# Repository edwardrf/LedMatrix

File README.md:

# LedMatrix
=======
8x8 Led Matrix project with microphone, light sensor and accelerometer

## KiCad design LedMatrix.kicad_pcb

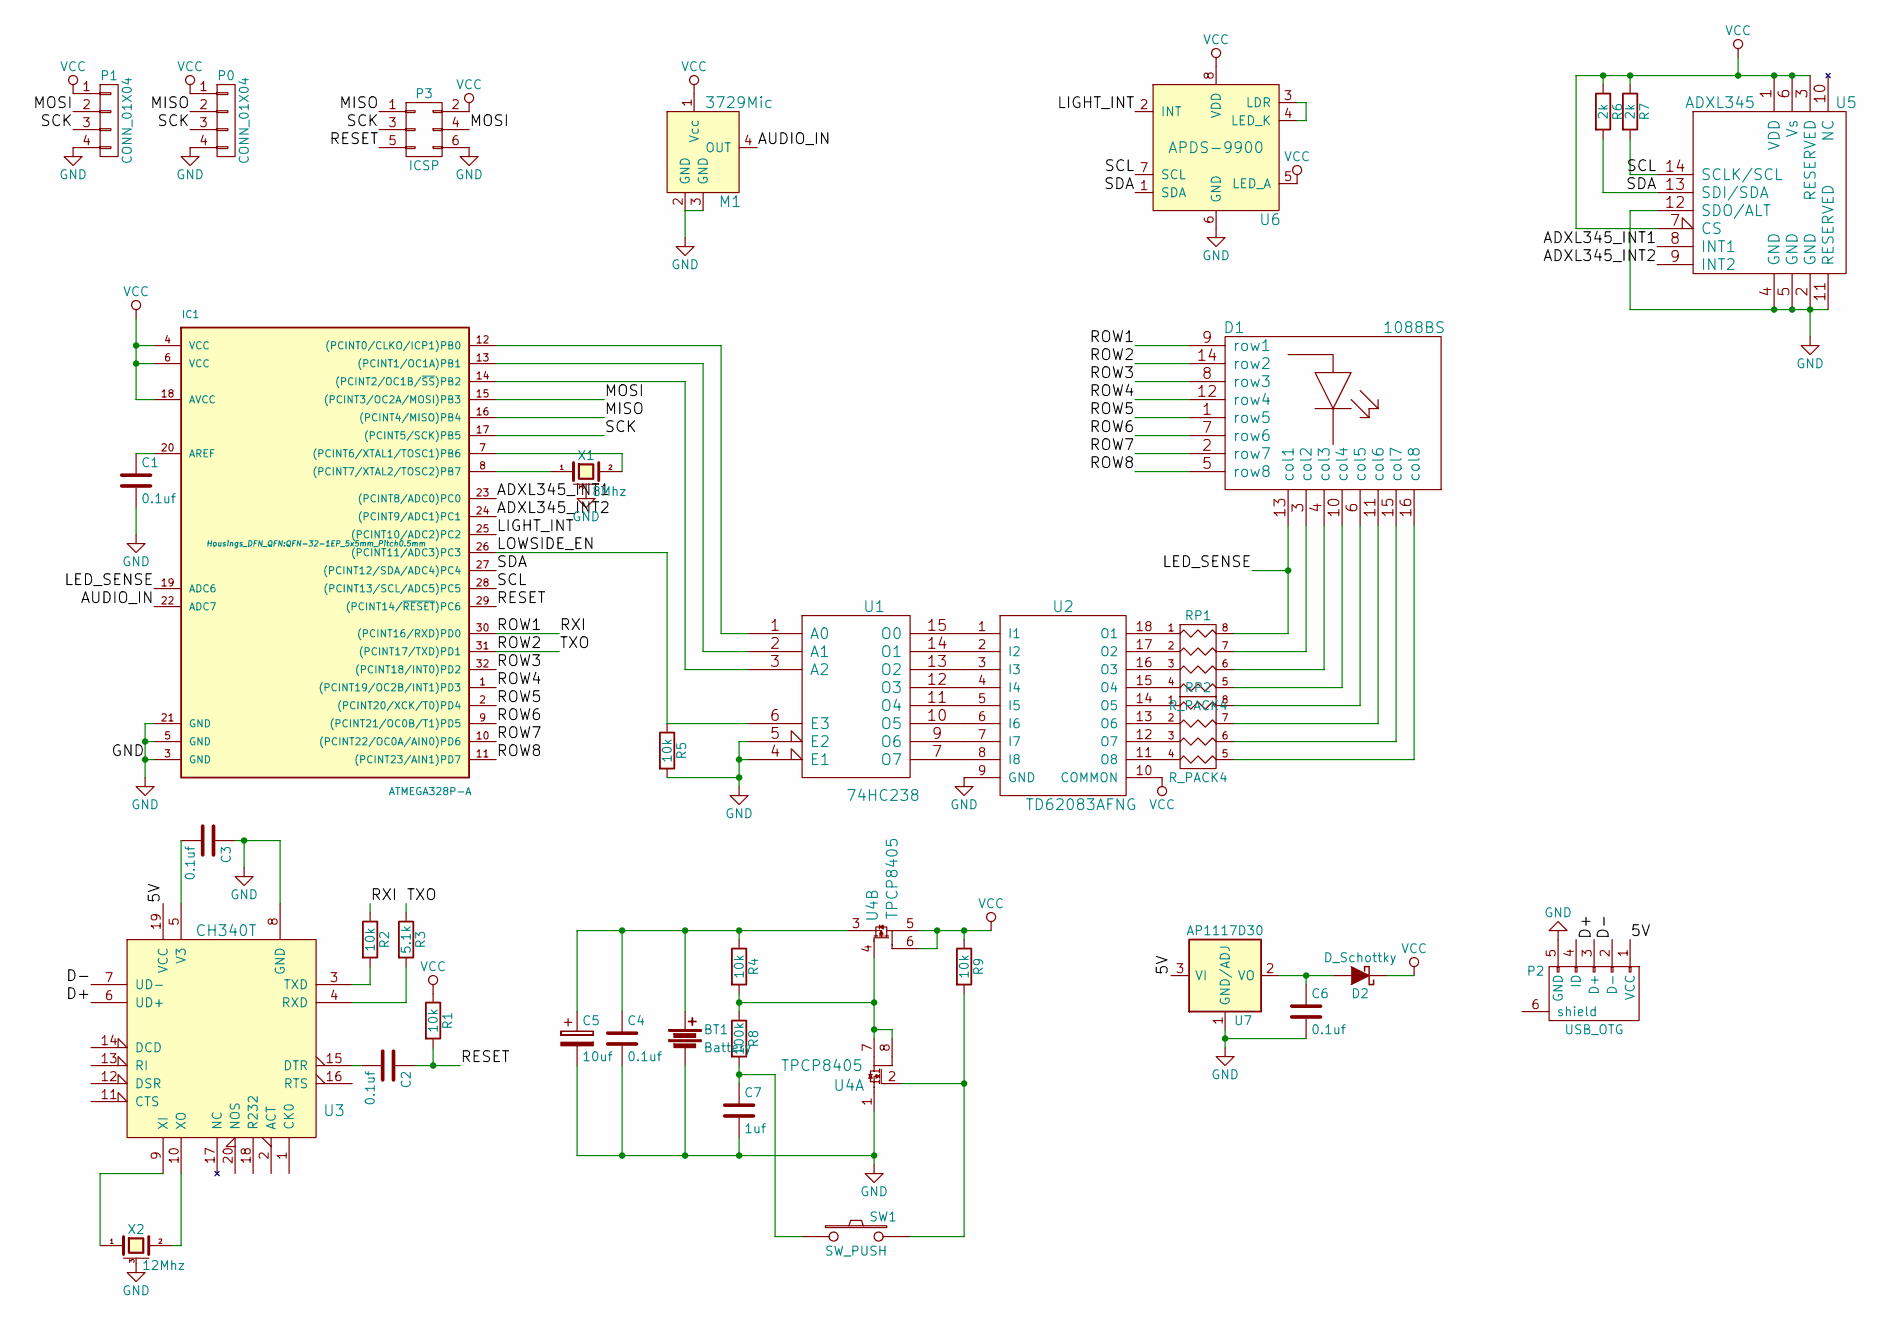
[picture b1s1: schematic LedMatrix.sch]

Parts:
BT1: Battery; CR2032-S8421-45R
C1, C2, C3, C4, C6: 0.1uf; C_0603
C5: 10uf; TantalC_SizeR_EIA-2012
C7: 1uf; C_0603
D1: 1088BS; 8X8 LED 32mm
D2: D_Schottky; SMA_Standard
IC1: ATMEGA328P-A; QFN-32-1EP_5x5mm_Pitch0.5mm
M1: 3729Mic
P0, P1: CONN_01X04; Pin_Header_Straight_1x04
P2: USB_OTG; 47589-0001
P3: ICSP; Pin_Header_Straight_2x03
R1, R2, R4, R5, R9: 10k; R_0603
R3: 5.1k; R_0603
R6, R7: 2k; R_0603
R8: 100k; R_0603
RP1, RP2: R_PACK4; R_Array_Concave_4x0603
SW1: SW_PUSH; SKSCLCE010
U1: 74HC238; TSSOP-16_4.4x5mm_Pitch0.65mm
U2: TD62083AFNG; TSSOP-14_4.4x5mm_Pitch0.65mm
U3: CH340T; SSOP-20_5.3x7.2mm_Pitch0.65mm
U4: TPCP8405; PS-8
U5: ADXL345
U6: APDS-9900; ADPS-9900
U7: AP1117D30; SOT-223
X1: 8Mhz; CSTCE8M00G52
X2: 12Mhz; CSTCE8M00G52

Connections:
/5V: P2.1 (VCC), U3.19 (VCC), U7.3 (VI)
/ADXL345_INT1: IC1.23 ((PCINT8/ADC0)PC0), U5.8 (INT1)
/ADXL345_INT2: IC1.24 ((PCINT9/ADC1)PC1), U5.9 (INT2)
/AUDIO_IN: IC1.22 (ADC7), M1.4 (OUT)
/D+: P2.3 (D+), U3.6 (UD+)
/D-: P2.2 (D-), U3.7 (UD-)
/LED_SENSE: D1.13 (col1), IC1.19 (ADC6), RP1.8 (R1)
/LIGHT_INT: IC1.25 ((PCINT10/ADC2)PC2), U6.2 (INT)
/LOWSIDE_EN: IC1.26 ((PCINT11/ADC3)PC3), R5.1, U1.6 (E3)
/MISO: IC1.16 ((PCINT4/MISO)PB4), P0.2, P3.1
/MOSI: IC1.15 ((PCINT3/OC2A/MOSI)PB3), P1.2, P3.4
/RESET: C2.1, IC1.29 ((PCINT14/~RESET~)PC6), P3.5, R1.2
/ROW1: D1.9 (row1), IC1.30 ((PCINT16/RXD)PD0), R2.1
/ROW2: D1.14 (row2), IC1.31 ((PCINT17/TXD)PD1), R3.1
/ROW3: D1.8 (row3), IC1.32 ((PCINT18/INT0)PD2)
/ROW4: D1.12 (row4), IC1.1 ((PCINT19/OC2B/INT1)PD3)
/ROW5: D1.1 (row5), IC1.2 ((PCINT20/XCK/T0)PD4)
/ROW6: D1.7 (row6), IC1.9 ((PCINT21/OC0B/T1)PD5)
/ROW7: D1.2 (row7), IC1.10 ((PCINT22/OC0A/AIN0)PD6)
/ROW8: D1.5 (row8), IC1.11 ((PCINT23/AIN1)PD7)
/SCK: IC1.17 ((PCINT5/SCK)PB5), P0.3, P1.3, P3.3
/SCL: IC1.28 ((PCINT13/SCL/ADC5)PC5), R7.2, U5.14 (SCLK/SCL), U6.7 (SCL)
/SDA: IC1.27 ((PCINT12/SDA/ADC4)PC4), R6.2, U5.13 (SDI/SDA), U6.1 (SDA)
GND: BT1.2, C1.2, C3.1, C4.2, C5.2, C6.2, C7.2, IC1.3 (GND), IC1.5 (GND), IC1.21 (GND), M1.2 (GND), M1.3 (GND), P0.4, P1.4, P2.5 (GND), P3.6, R5.2, U1.4 (E1), U1.5 (E2), U1.8 (GND), U2.9 (GND), U3.8 (GND), U4.1, U5.2 (GND), U5.4 (GND), U5.5 (GND), U5.11 (RESERVED), U5.12 (SDO/ALT), U6.6 (GND), U7.1 (GND/ADJ), X1.3 (case), X2.3 (case)
unnamed: BT1.1, C4.1, C5.1, R4.1, U4.3
unnamed: C1.1, IC1.20 (AREF)
unnamed: C2.2, U3.15 (DTR)
unnamed: C3.2, U3.5 (V3)
unnamed: C6.1, D2.2 (A), U7.2 (VO)
unnamed: C7.1, R8.2, SW1.1
unnamed: D1.3 (col2), RP1.7 (R2)
unnamed: D1.4 (col3), RP1.6 (R3)
unnamed: D1.6 (col5), RP2.8 (R1)
unnamed: D1.10 (col4), RP1.5 (R4)
unnamed: D1.11 (col6), RP2.7 (R2)
unnamed: D1.15 (col7), RP2.6 (R3)
unnamed: D1.16 (col8), RP2.5 (R4)
unnamed: IC1.7 ((PCINT6/XTAL1/TOSC1)PB6), X1.2
unnamed: IC1.8 ((PCINT7/XTAL2/TOSC2)PB7), X1.1
unnamed: IC1.12 ((PCINT0/CLKO/ICP1)PB0), U1.1 (A0)
unnamed: IC1.13 ((PCINT1/OC1A)PB1), U1.2 (A1)
unnamed: IC1.14 ((PCINT2/OC1B/~SS~)PB2), U1.3 (A2)
unnamed: R2.2, U3.3 (TXD)
unnamed: R3.2, U3.4 (RXD)
unnamed: R4.2, R8.1, U4.4, U4.7, U4.8
unnamed: R9.2, SW1.2, U4.2
unnamed: RP1.1, U2.18 (O1)
unnamed: RP1.2, U2.17 (O2)
unnamed: RP1.3, U2.16 (O3)
unnamed: RP1.4, U2.15 (O4)
unnamed: RP2.1, U2.14 (O5)
unnamed: RP2.2, U2.13 (O6)
unnamed: RP2.3, U2.12 (O7)
unnamed: RP2.4, U2.11 (O8)
unnamed: U1.7 (O7), U2.8 (I8)
unnamed: U1.9 (O6), U2.7 (I7)
unnamed: U1.10 (O5), U2.6 (I6)
unnamed: U1.11 (O4), U2.5 (I5)
unnamed: U1.12 (O3), U2.4 (I4)
unnamed: U1.13 (O2), U2.3 (I3)
unnamed: U1.14 (O1), U2.2 (I2)
unnamed: U1.15 (O0), U2.1 (I1)
unnamed: U3.9 (XI), X2.1
unnamed: U3.10 (XO), X2.2
unnamed: U6.3 (LDR), U6.4 (LED_K)
VCC: D2.1 (K), IC1.4 (VCC), IC1.6 (VCC), IC1.18 (AVCC), M1.1 (Vcc), P0.1, P1.1, P3.2, R1.1, R6.1, R7.1, R9.1, U1.16 (VCC), U2.10 (COMMON), U4.5, U4.6, U5.1 (VDD), U5.3 (RESERVED), U5.6 (Vs), U5.7 (CS), U6.5 (LED_A), U6.8 (VDD)

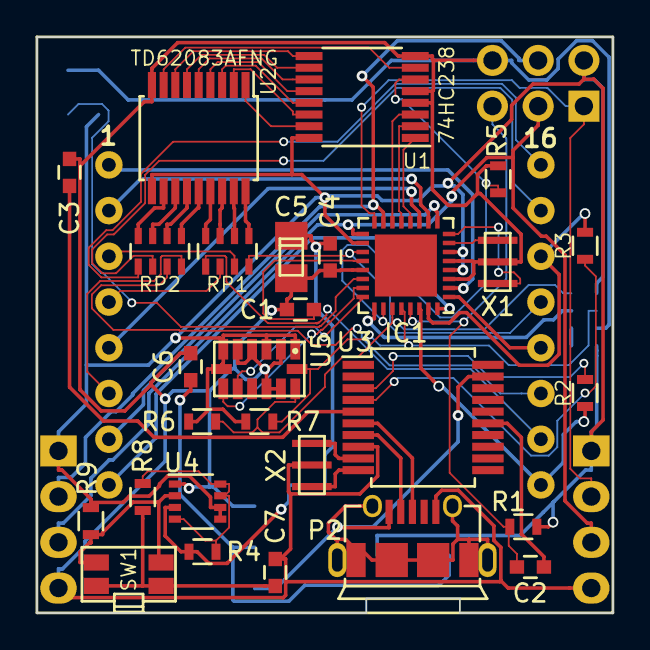
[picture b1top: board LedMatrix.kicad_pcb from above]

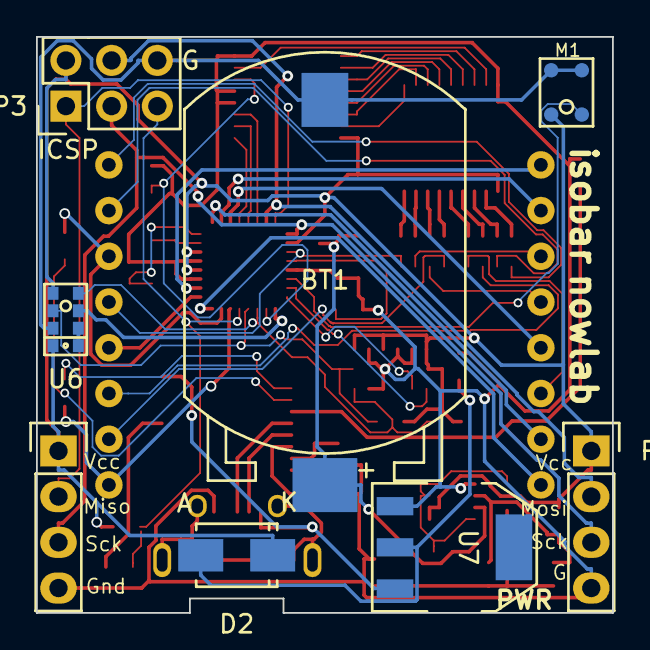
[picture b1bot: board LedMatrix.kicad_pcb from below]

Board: 2 copper layers, 32.0 x 32.0 mm, 37 parts (8 on the bottom side), 66 nets.

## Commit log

2015-08-04 Initial commit the TLC5917
2015-08-18 Update the LED control program
2015-08-18 Add simple readme
2015-08-26 Arduino program
2015-09-03 Use flash memory for animation
2015-09-03 change directory name
2015-09-15 accelerometer calibration
2015-09-15 Brightness code
2015-10-02 test ch340
2015-11-03 Add apds9900 lib
2015-11-03 main program update
2016-08-07 Add francis and northy mods
